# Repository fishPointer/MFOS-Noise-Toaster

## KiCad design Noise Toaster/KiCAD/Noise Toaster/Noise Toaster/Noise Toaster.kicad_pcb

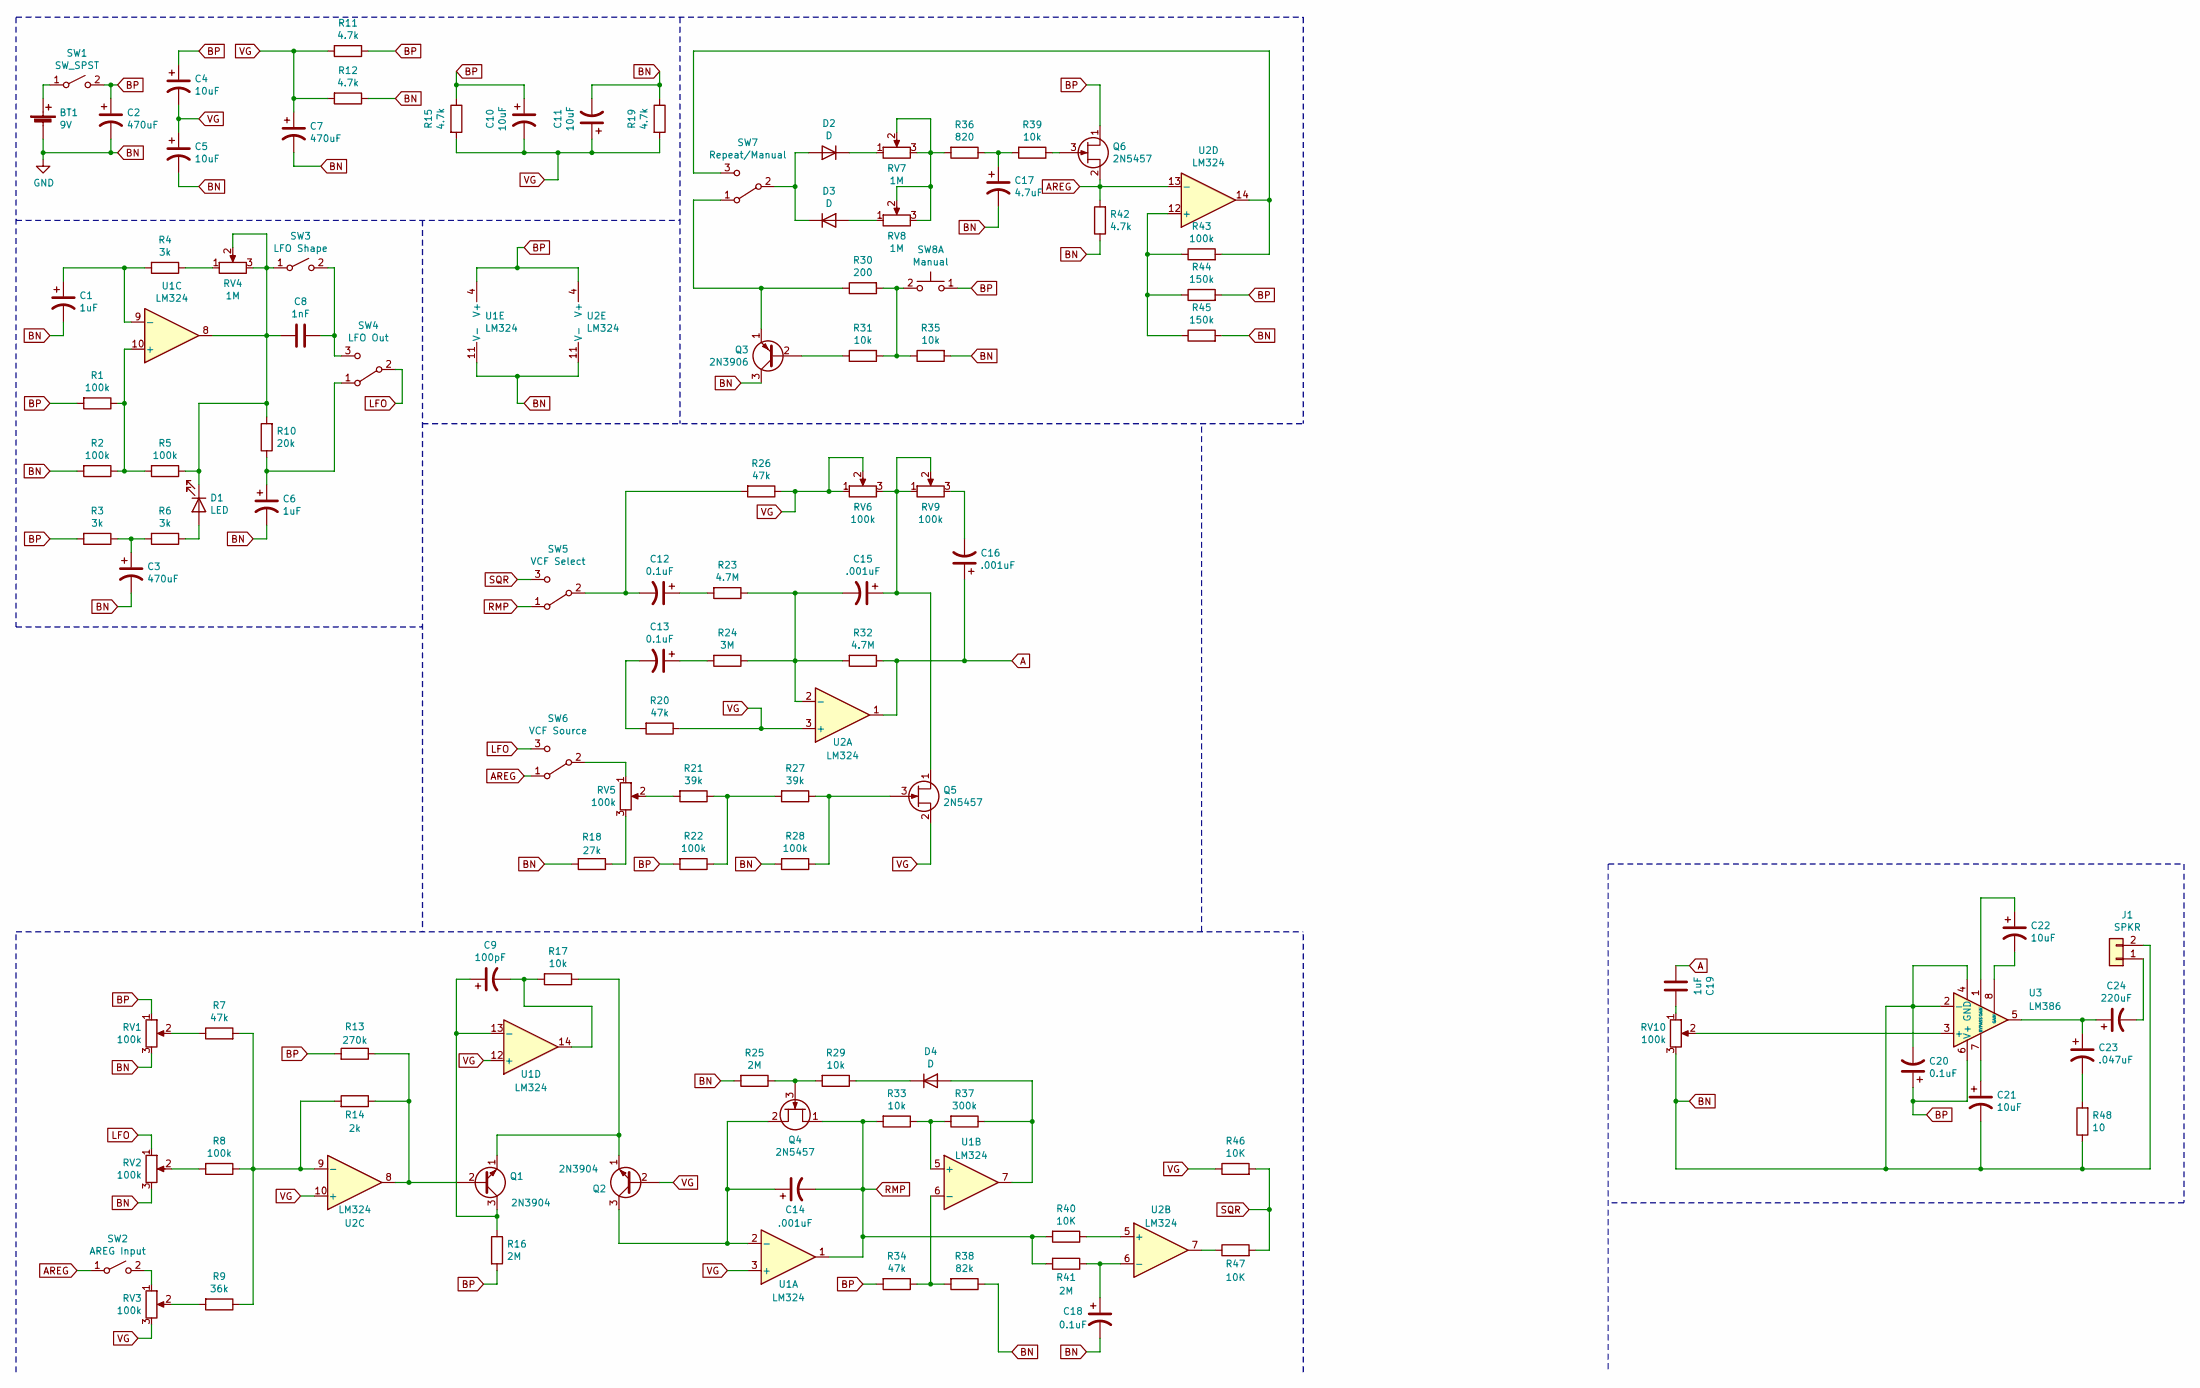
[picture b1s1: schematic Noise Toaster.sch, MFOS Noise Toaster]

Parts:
BT1: 9V; JST_EH_B2B-EH-A_1x02_P2.50mm_Vertical
C1, C6: 1uF; CP_Radial_D5.0mm_P2.00mm
C2, C3, C7: 470uF; CP_Radial_D10.0mm_P5.00mm
C4, C5, C10, C11, C21, C22: 10uF; CP_Radial_D5.0mm_P2.00mm
C8: 1nF; C_Disc_D4.7mm_W2.5mm_P5.00mm
C9: 100pF; C_Disc_D4.7mm_W2.5mm_P5.00mm
C12, C13, C18, C20: 0.1uF; CP_Radial_D5.0mm_P2.00mm
C14, C15, C16: .001uF; C_Disc_D4.7mm_W2.5mm_P5.00mm
C17: 4.7uF; CP_Radial_D5.0mm_P2.00mm
C19: 1uF; C_Disc_D4.7mm_W2.5mm_P5.00mm
C23: .047uF; C_Disc_D4.7mm_W2.5mm_P5.00mm
C24: 220uF; CP_Radial_D10.0mm_P5.00mm
D1: LED; LED_D3.0mm
D2, D3, D4: D; D_A-405_P7.62mm_Horizontal
J1: SPKR; JST_EH_B2B-EH-A_1x02_P2.50mm_Vertical
Q1, Q2: 2N3904; TO-92_Inline
Q3: 2N3906; TO-92_Inline
Q4, Q5, Q6: 2N5457; TO-92_Inline
R1, R2, R5, R8, R22, R28, R43: 100k; R_Axial_DIN0207_L6.3mm_D2.5mm_P7.62mm_Horizontal
R3, R4, R6: 3k; R_Axial_DIN0207_L6.3mm_D2.5mm_P7.62mm_Horizontal
R7, R20, R26, R34: 47k; R_Axial_DIN0207_L6.3mm_D2.5mm_P7.62mm_Horizontal
R9: 36k; R_Axial_DIN0207_L6.3mm_D2.5mm_P7.62mm_Horizontal
R10: 20k; R_Axial_DIN0207_L6.3mm_D2.5mm_P7.62mm_Horizontal
R11, R12, R15, R19, R42: 4.7k; R_Axial_DIN0207_L6.3mm_D2.5mm_P7.62mm_Horizontal
R13: 270k; R_Axial_DIN0207_L6.3mm_D2.5mm_P7.62mm_Horizontal
R14: 2k; R_Axial_DIN0207_L6.3mm_D2.5mm_P7.62mm_Horizontal
R16, R25, R41: 2M; R_Axial_DIN0207_L6.3mm_D2.5mm_P7.62mm_Horizontal
R17, R29, R31, R33, R35, R39: 10k; R_Axial_DIN0207_L6.3mm_D2.5mm_P7.62mm_Horizontal
R18: 27k; R_Axial_DIN0207_L6.3mm_D2.5mm_P7.62mm_Horizontal
R21, R27: 39k; R_Axial_DIN0207_L6.3mm_D2.5mm_P7.62mm_Horizontal
R23, R32: 4.7M; R_Axial_DIN0207_L6.3mm_D2.5mm_P7.62mm_Horizontal
R24: 3M; R_Axial_DIN0207_L6.3mm_D2.5mm_P7.62mm_Horizontal
R30: 200; R_Axial_DIN0207_L6.3mm_D2.5mm_P7.62mm_Horizontal
R36: 820; R_Axial_DIN0207_L6.3mm_D2.5mm_P7.62mm_Horizontal
R37: 300k; R_Axial_DIN0207_L6.3mm_D2.5mm_P7.62mm_Horizontal
R38: 82k; R_Axial_DIN0207_L6.3mm_D2.5mm_P7.62mm_Horizontal
R40, R46, R47: 10K; R_Axial_DIN0207_L6.3mm_D2.5mm_P7.62mm_Horizontal
R44, R45: 150k; R_Axial_DIN0207_L6.3mm_D2.5mm_P7.62mm_Horizontal
R48: 10; R_Axial_DIN0207_L6.3mm_D2.5mm_P7.62mm_Horizontal
RV1, RV2, RV3, RV5, RV6, RV9, RV10: 100k; JST_EH_B3B-EH-A_1x03_P2.50mm_Vertical
RV4, RV7, RV8: 1M; JST_EH_B3B-EH-A_1x03_P2.50mm_Vertical
SW1: SW_SPST; JST_EH_B3B-EH-A_1x03_P2.50mm_Vertical
SW2: AREG Input; JST_EH_B3B-EH-A_1x03_P2.50mm_Vertical
SW3: LFO Shape; JST_EH_B3B-EH-A_1x03_P2.50mm_Vertical
SW4: LFO Out; JST_EH_B3B-EH-A_1x03_P2.50mm_Vertical
SW5: VCF Select; JST_EH_B3B-EH-A_1x03_P2.50mm_Vertical
SW6: VCF Source; JST_EH_B3B-EH-A_1x03_P2.50mm_Vertical
SW7: Repeat/Manual; JST_EH_B3B-EH-A_1x03_P2.50mm_Vertical
SW8: Manual; JST_EH_B3B-EH-A_1x03_P2.50mm_Vertical
U1, U2: LM324; DIP-14_W7.62mm
U3: LM386; DIP-8_W7.62mm

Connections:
A: C16.1, C19.2, R32.1, U2.1
AREG: Q6.2 (S), R42.2, SW2.1 (A), SW6.1 (A), U2.13 (-)
BN: BT1.2 (-), C1.2, C2.2, C3.2, C5.2, C6.2, C7.2, C11.2, C17.2, C18.2, C20.2, C21.2, J1.2, Q3.3 (C), R2.2, R12.1, R18.2, R19.1, R25.2, R28.2, R35.2, R38.1, R42.1, R45.2, R48.1, RV1.3, RV2.3, RV10.3, U1.11 (V-), U2.11 (V-), U3.2 (-), U3.4 (GND)
BP: C2.1, C4.1, C10.1, C20.1, Q6.1 (D), R1.2, R3.2, R11.1, R13.2, R15.1, R16.2, R22.2, R34.2, R44.2, RV1.1, SW1.2 (B), SW8.1 (C), U1.4 (V+), U2.4 (V+), U3.6 (V+)
LFO: RV2.1, SW4.2 (B), SW6.3 (C)
unnamed: BT1.1 (+), SW1.1 (A)
unnamed: C1.1, R4.2, U1.9 (-)
unnamed: C3.1, R3.1, R6.2
unnamed: C6.1, R10.1, SW4.1 (A)
unnamed: C8.1, SW3.2 (B), SW4.3 (C)
unnamed: C8.2, D1.1 (K), R5.1, R10.2, RV4.2, RV4.3, SW3.1 (A), U1.8
unnamed: C9.1, Q1.3 (C), R16.1, U1.13 (-)
unnamed: C9.2, R17.2, U1.14
unnamed: C12.1, R23.2
unnamed: C12.2, R26.2, SW5.2 (B)
unnamed: C13.1, R24.2
unnamed: C13.2, R20.2
unnamed: C14.1, Q2.3 (C), Q4.2 (S), U1.2 (-)
unnamed: C15.1, Q5.1 (D), RV6.3, RV9.1, RV9.2
unnamed: C15.2, R23.1, R24.1, R32.2, U2.2 (-)
unnamed: C16.2, RV9.3
unnamed: C17.1, R36.1, R39.2
unnamed: C18.1, R41.1, U2.6 (-)
unnamed: C19.1, RV10.1
unnamed: C21.1, U3.7 (BYPASS)
unnamed: C22.1, U3.1 (GAIN)
unnamed: C22.2, U3.8 (GAIN)
unnamed: C23.1, C24.1, U3.5
unnamed: C23.2, R48.2
unnamed: C24.2, J1.1
unnamed: D1.2 (A), R6.1
unnamed: D2.1 (K), RV7.1
unnamed: D2.2 (A), D3.1 (K), SW7.2 (B)
unnamed: D3.2 (A), RV8.1
unnamed: D4.1 (K), R29.1
unnamed: D4.2 (A), R37.1, U1.7
unnamed: Q1.1 (E), Q2.1 (E), R17.1
unnamed: Q1.2 (B), R13.1, R14.1, U2.8
unnamed: Q3.1 (E), R30.1, SW7.1 (A)
unnamed: Q3.2 (B), R31.1
unnamed: Q4.3 (G), R25.1, R29.2
unnamed: Q5.3 (G), R27.1, R28.1
unnamed: Q6.3 (G), R39.1
unnamed: R1.1, R2.1, R5.2, U1.10 (+)
unnamed: R4.1, RV4.1
unnamed: R7.1, RV1.2
unnamed: R8.2, RV2.2
unnamed: R9.2, RV3.2
unnamed: R7.2, R8.1, R9.1, R14.2, U2.9 (-)
unnamed: R18.1, RV5.3
unnamed: R21.1, R22.1, R27.2
unnamed: R21.2, RV5.2
unnamed: R30.2, R31.2, R35.1, SW8.2 (D)
unnamed: R33.1, R37.2, U1.5 (+)
unnamed: R34.1, R38.2, U1.6 (-)
unnamed: R36.2, RV7.2, RV7.3, RV8.2, RV8.3
unnamed: R40.1, U2.5 (+)
unnamed: R43.1, R44.1, R45.1, U2.12 (+)
unnamed: R43.2, SW7.3 (C), U2.14
unnamed: R47.1, U2.7
unnamed: RV3.1, SW2.2 (B)
unnamed: RV5.1, SW6.2 (B)
unnamed: RV10.2, U3.3 (+)
RMP: C14.2, Q4.1 (D), R33.2, R40.2, R41.2, SW5.1 (A), U1.1
SQR: R46.2, R47.2, SW5.3 (C)
VG: C4.2, C5.1, C7.1, C10.2, C11.1, Q2.2 (B), Q5.2 (S), R11.2, R12.2, R15.2, R19.2, R20.1, R26.1, R46.1, RV3.3, RV6.1, RV6.2, U1.3 (+), U1.12 (+), U2.3 (+), U2.10 (+)

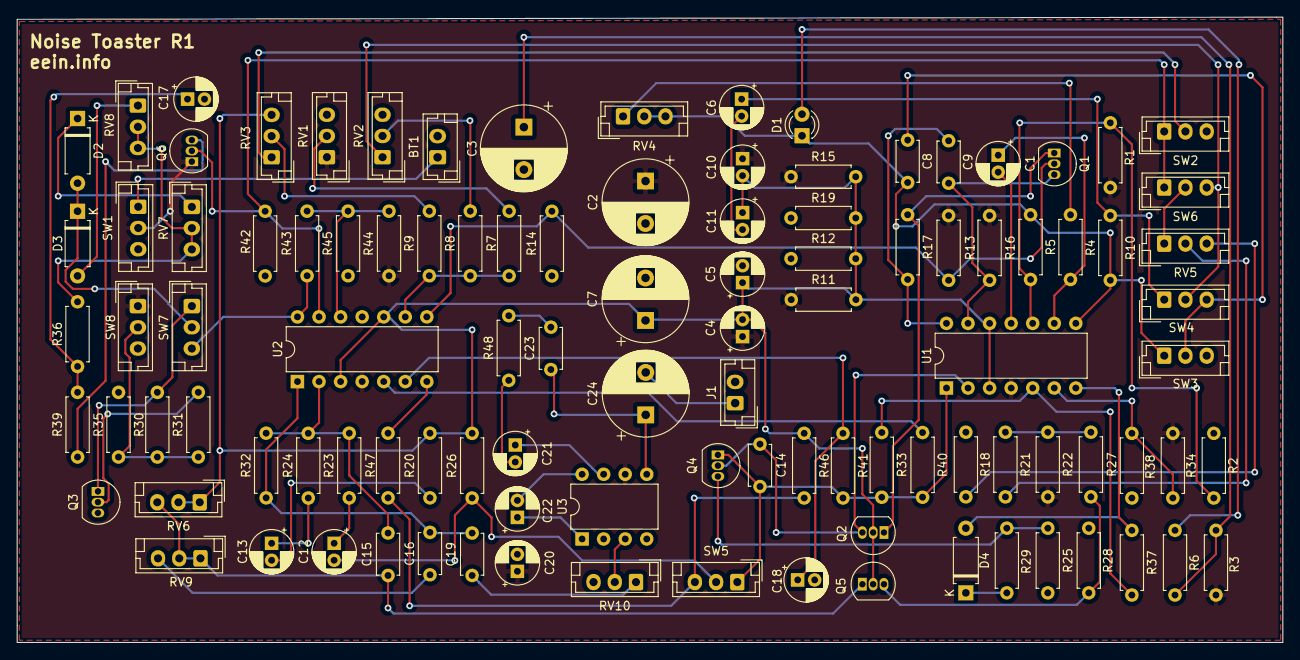
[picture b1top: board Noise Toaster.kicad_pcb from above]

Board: 2 copper layers, 149.1 x 73.7 mm, 105 parts (0 on the bottom side), 66 nets.

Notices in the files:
Noise Toaster/KiCAD/Noise Toaster/Noise Toaster/Noise Toaster.sch:
creativecommons.org/licenses/by/4.0
License: CC BY 4.0
